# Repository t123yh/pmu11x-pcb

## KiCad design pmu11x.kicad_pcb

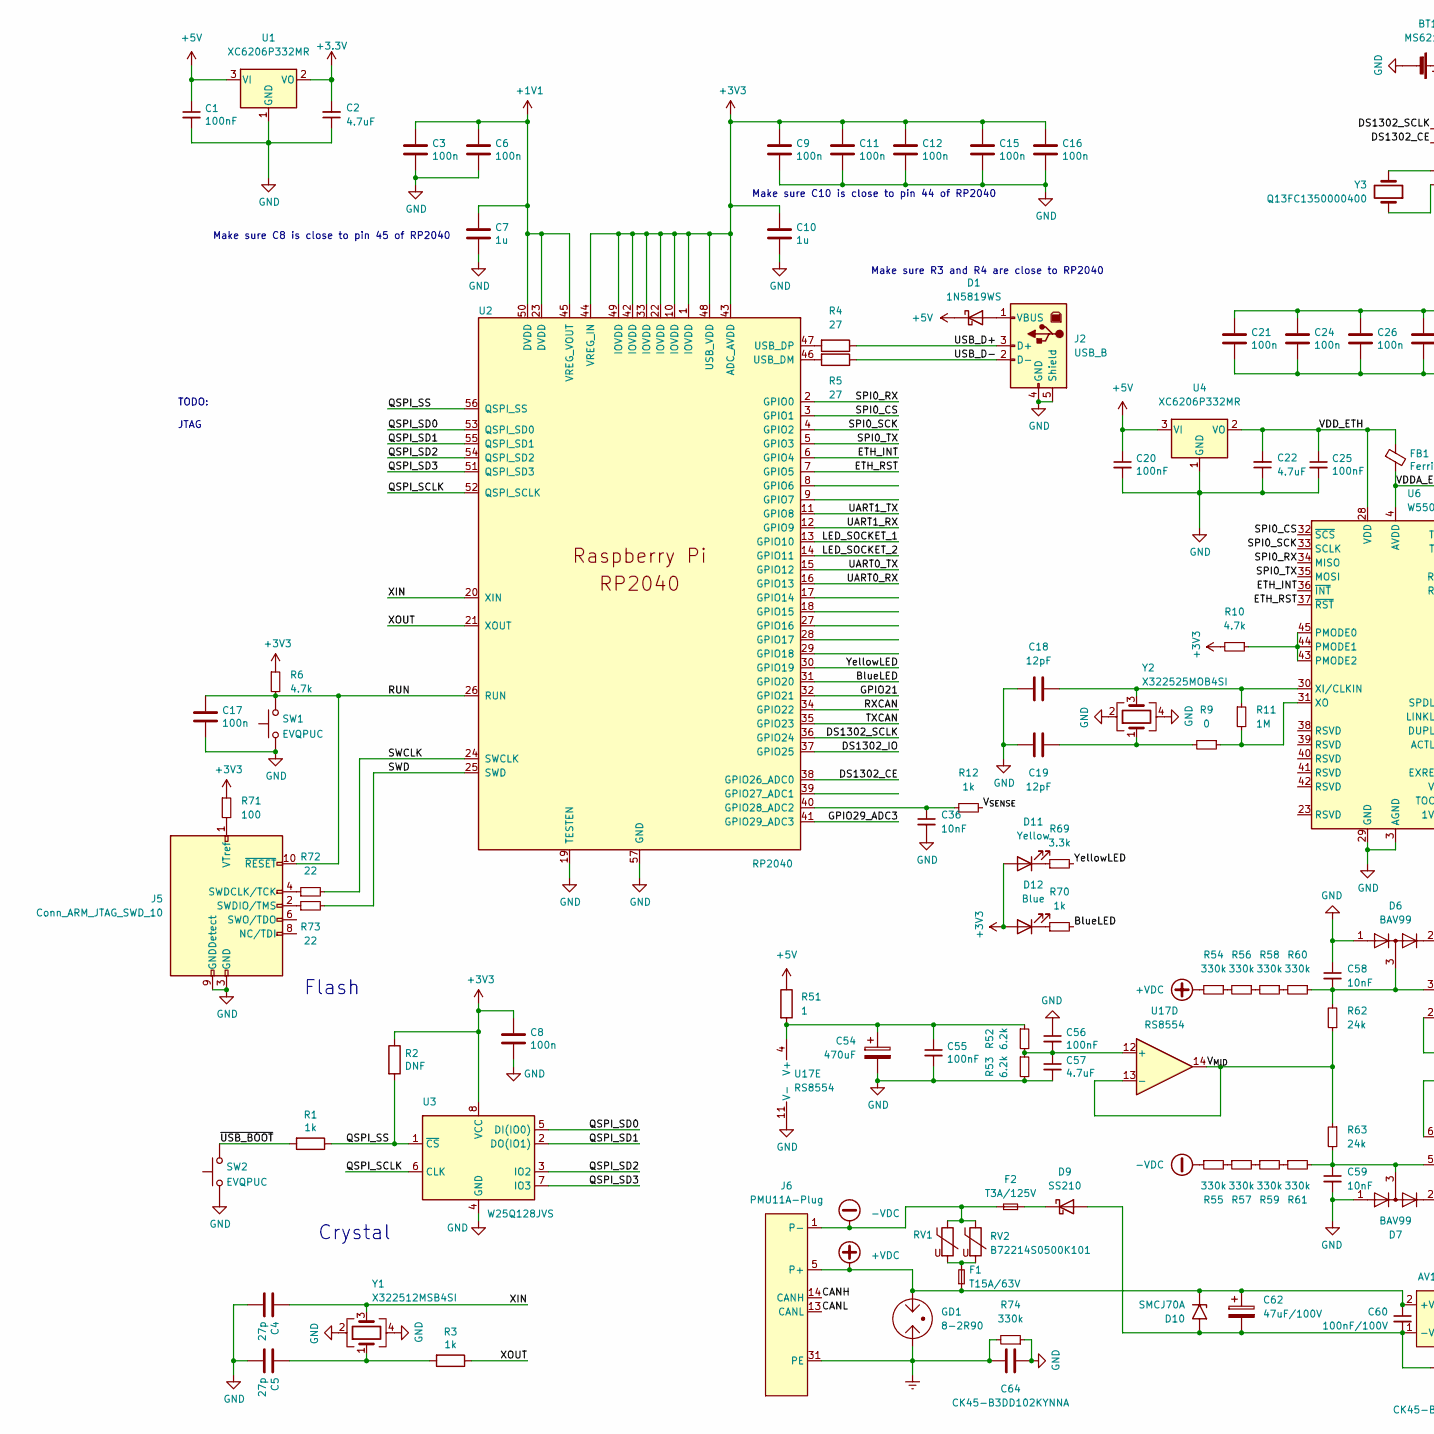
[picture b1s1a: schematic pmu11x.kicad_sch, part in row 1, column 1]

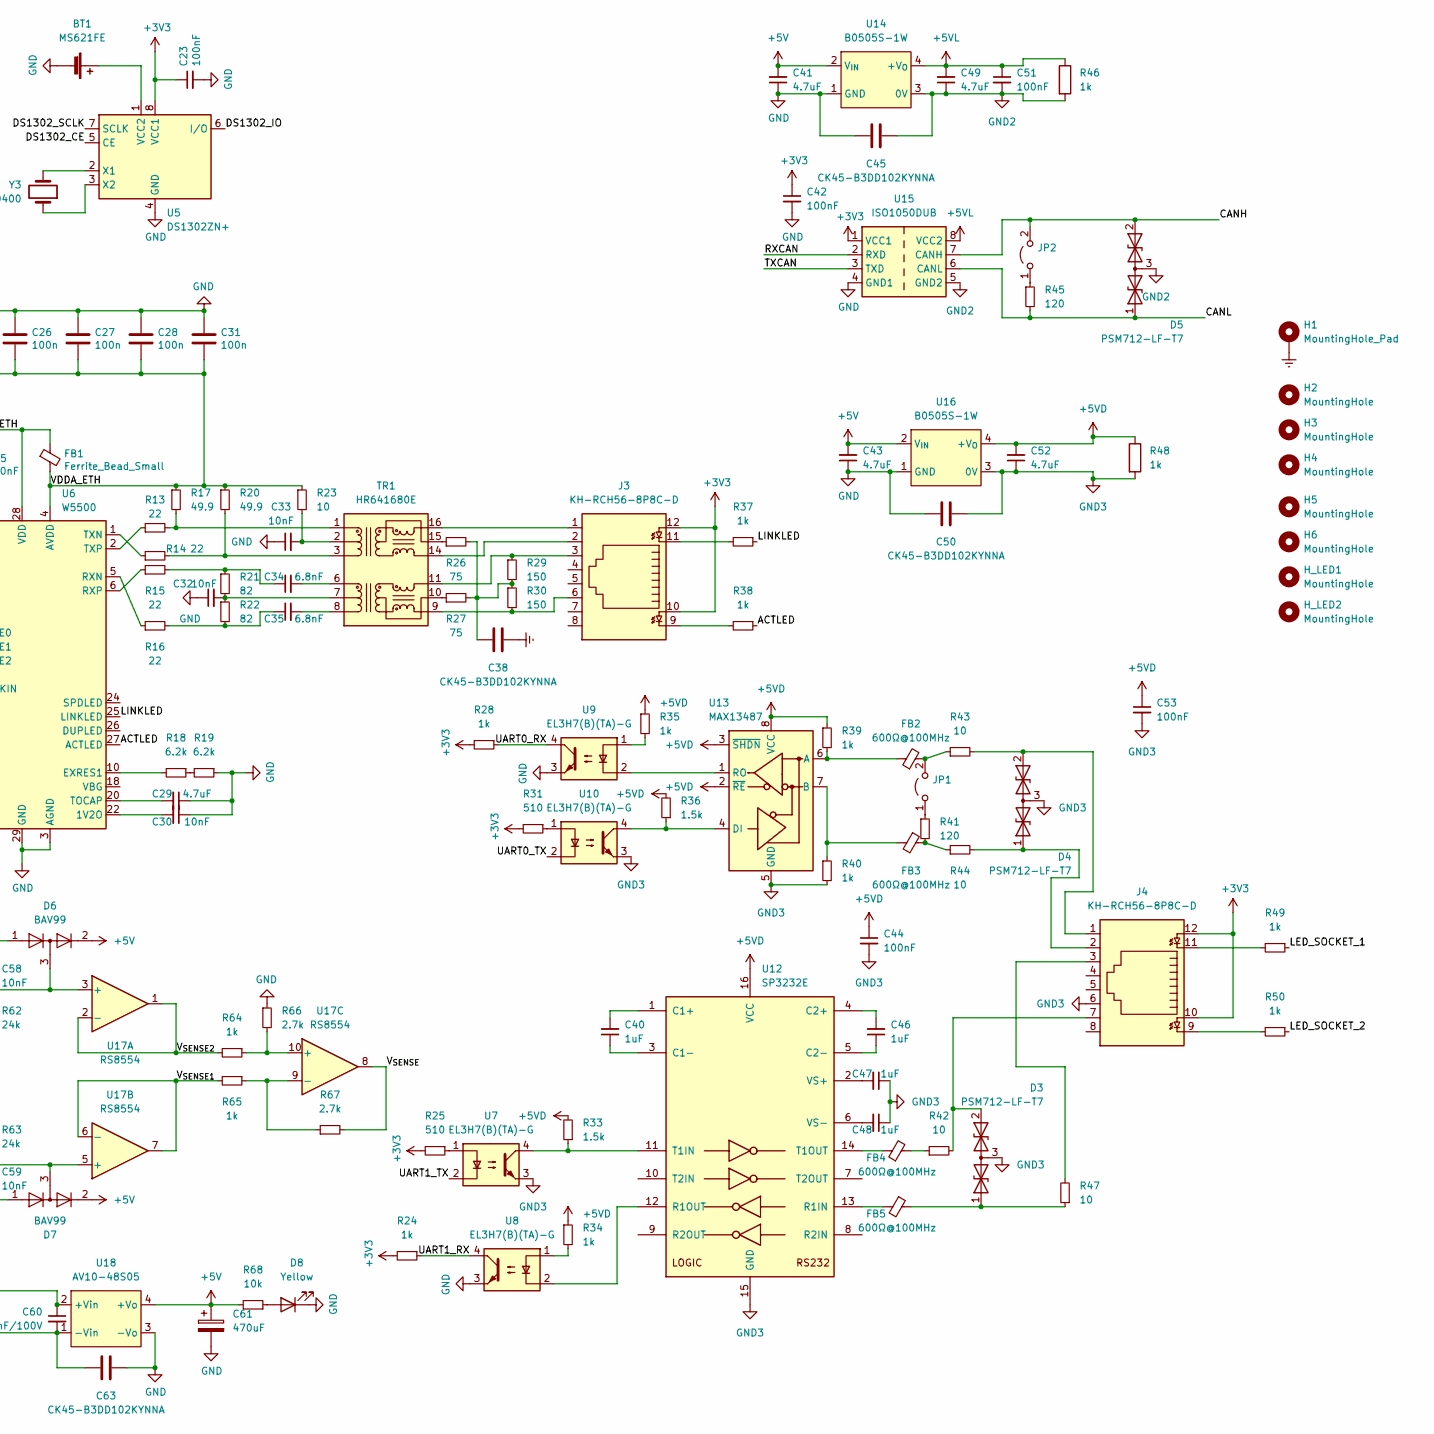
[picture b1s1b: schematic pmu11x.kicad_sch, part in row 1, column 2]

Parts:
BT1: MS621FE; BatteryHolder_Seiko_MS621F
C1: 100nF; 0603_C
C2, C22, C29, C41, C43, C49, C52, C57: 4.7uF; 0603_C
C3, C6, C8, C9, C11, C12, C15, C16, C17, C21, C24, C26, C27, C28, C31: 100n; 0402_C
C4, C5: 27p; 0402_C
C7, C10: 1u; 0402_C
C18, C19: 12pF; 0402_C
C20, C23, C25, C42, C44, C51, C53, C55, C56: 100nF; 0402_C
C30, C32, C33, C36: 10nF; 0402_C
C34, C35: 6.8nF; 0603_C
C38, C45, C50, C63, C64: CK45-B3DD102KYNNA; C_Disc_D7.5mm_W2.5mm_P5.00mm
C40, C46, C47, C48: 1uF; 0603_C
C54, C61: 470uF; CP_Radial_D6.3mm_P2.50mm
C58, C59: 10nF; 0603_C
C60: 100nF/100V; 0805_C
C62: 47uF/100V; CP_Radial_D8.0mm_P3.50mm
D1: 1N5819WS; SOD-323
D3, D4, D5: PSM712-LF-T7; SOT-23-3L
D6, D7: BAV99; SOT-23
D8, D11: Yellow; 0603_LED_S1_NUM
D9: SS210; D_SMA
D10: SMCJ70A; D_SMC
D12: Blue; 0603_LED_S1_NUM
F1: T15A/63V; Fuse_1812_4532Metric
F2: T3A/125V; Fuse_1812_4532Metric
FB1: Ferrite_Bead_Small; 0603_C
FB2, FB3, FB4, FB5: 600Ω@100MHz; 0603_R
GD1: 8-2R90; GDT_10KA
H1: MountingHole_Pad; MountingHole_3.5mm_Pad_Via
H2, H3, H4, H5, H6: MountingHole; MountingHole_3.5mm_Pad
H_LED1: MountingHole; MountingHole_3mm
H_LED2: MountingHole; MountingHole_2.2mm_M2
J2: USB_B; USB_B_OST_USB-B1HSxx_Horizontal
J3, J4: KH-RCH56-8P8C-D
J5: Conn_ARM_JTAG_SWD_10; PinSocket_2x05_P1.27mm_Vertical
J6: PMU11A-Plug
JP1, JP2: Jumper_2_Open; SolderJumper-2_P1.3mm_Open_RoundedPad1.0x1.5mm
R1, R3, R12, R24, R28, R34, R35, R37, R38, R39, R40, R49, R50, R64, R65, R70: 1k; 0402_R
R2: DNF; 0402_R
R4, R5: 27; 0402_R
R6, R10: 4.7k; 0402_R
R9: 0; 0402_R
R11: 1M; 0402_R
R13, R14, R15, R16, R72, R73: 22; 0402_R
R17, R20: 49.9; 0603_R
R18, R19, R52, R53: 6.2k; 0603_R
R21, R22: 82; 0603_R
R23: 10; 0402_R
R25, R31: 510; 0402_R
R26, R27: 75; 0603_R
R29, R30: 150; 0603_R
R33, R36: 1.5k; 0402_R
R41, R45: 120; 0603_R
R42, R43, R44, R47: 10; 0603_R
R46, R48: 1k; 0603_R
R51: 1; 0603_R
R54, R55, R56, R57, R58, R59, R60, R61, R74: 330k; 0805_R
R62, R63: 24k; 0805_R
R66, R67: 2.7k; 0603_R
R68: 10k; 0402_R
R69: 3.3k; 0402_R
R71: 100; 0402_R
RV1, RV2: B72214S0500K101; RV_Disc_D15.5mm_W4.6mm_P7.5mm
SW1, SW2: EVQPUC; Panasonic_EVQPUL_EVQPUC
TR1: HR641680E; Transformer_Ethernet_Bourns_PT61017PEL
U1, U4: XC6206P332MR; SOT-23-3L
U2: RP2040; RP2040-QFN-56
U3: W25Q128JVS; SOIC-8_5.23x5.23mm_P1.27mm
U5: DS1302ZN+; SOIC-8_3.9x4.9mm_P1.27mm
U6: W5500; LQFP-48_7x7mm_P0.5mm
U7, U8, U9, U10: EL3H7(B)(TA)-G; SOP-4_4.4x2.6mm_P1.27mm
U12: SP3232E; SOIC-16_3.9x9.9mm_P1.27mm
U13: MAX13487; SOIC-8_3.9x4.9mm_P1.27mm
U14, U16: B0505S-1W; B_S-1W
U15: ISO1050DUB; SOP-8_6.62x9.15mm_P2.54mm
U17: RS8554; TSSOP-14_4.4x5mm_P0.65mm
U18: AV10-48S05; AV10-48Sxx
Y1: X322512MSB4SI; Oscillator_SMD_Abracon_ASE-4Pin_3.2x2.5mm
Y2: X322525MOB4SI; Oscillator_SMD_Abracon_ASE-4Pin_3.2x2.5mm
Y3: Q13FC1350000400; Crystal_SMD_3215-2Pin_3.2x1.5mm

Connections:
+1V1: C3.1, C6.1, C7.1, U2.23 (DVDD), U2.45 (VREG_VOUT), U2.50 (DVDD)
+5V: C1.1, C20.1, C41.2, C43.2, C61.1, D1.1 (K), D6.2 (A), D7.2 (A), R51.1, R68.2, U1.3 (VI), U4.3 (VI), U14.2 (V_{IN}), U16.2 (V_{IN}), U18.4 (+Vo)
+5VD: C44.1, C52.2, C53.1, R33.2, R34.1, R35.1, R36.2, R39.1, R48.1, U12.16 (VCC), U13.2 (~RE), U13.3 (~SHDN), U13.8 (VCC), U16.4 (+V_{O})
+5VL: C49.2, C51.1, R46.1, U14.4 (+V_{O}), U15.8 (VCC2)
+VDC: C60.1, C62.1, D10.1 (A1), F1.1, GD1.3, J6.5 (P+), R54.2, U18.2 (+Vin)
-VDC: F2.2, J6.1 (P-), R55.1, RV1.1, RV2.1
/ACTLED: R38.1, U6.27 (ACTLED)
/BlueLED: R70.2, U2.31 (GPIO20)
/CANH: D5.2 (A2), J6.14 (CANH), JP2.2 (B), U15.7 (CANH)
/CANL: D5.1 (A1), J6.13 (CANL), R45.2, U15.6 (CANL)
/DS1302_CE: U2.38 (GPIO26_ADC0), U5.5 (CE)
/DS1302_IO: U2.37 (GPIO25), U5.6 (I/O)
/DS1302_SCLK: U2.36 (GPIO24), U5.7 (SCLK)
/ETH_INT: U2.6 (GPIO4), U6.36 (~INT)
/ETH_RST: U2.7 (GPIO5), U6.37 (~RST)
/GPIO21: U2.32 (GPIO21)
/GPIO29_ADC3: U2.41 (GPIO29_ADC3)
/LED_SOCKET_1: R49.1, U2.13 (GPIO10)
/LED_SOCKET_2: R50.1, U2.14 (GPIO11)
/LINKLED: R37.1, U6.25 (LINKLED)
/QSPI_SCLK: U2.52 (QSPI_SCLK), U3.6 (CLK)
/QSPI_SD0: U2.53 (QSPI_SD0), U3.5 (DI(IO0))
/QSPI_SD1: U2.55 (QSPI_SD1), U3.2 (DO(IO1))
/QSPI_SD2: U2.54 (QSPI_SD2), U3.3 (IO2)
/QSPI_SD3: U2.51 (QSPI_SD3), U3.7 (IO3)
/QSPI_SS: R1.1, R2.2, U2.56 (QSPI_SS), U3.1 (~CS)
/RUN: C17.1, J5.10 (~RESET), R6.2, SW1.2, U2.26 (RUN)
/RXCAN: U2.34 (GPIO22), U15.2 (RXD)
/SPI0_CS: U2.3 (GPIO1), U6.32 (~SCS)
/SPI0_RX: U2.2 (GPIO0), U6.34 (MISO)
/SPI0_SCK: U2.4 (GPIO2), U6.33 (SCLK)
/SPI0_TX: U2.5 (GPIO3), U6.35 (MOSI)
/SWCLK: R72.2, U2.24 (SWCLK)
/SWD: R73.2, U2.25 (SWD)
/TXCAN: U2.35 (GPIO23), U15.3 (TXD)
/UART0_RX: R28.1, U2.16 (GPIO13), U9.4
/UART0_TX: U2.15 (GPIO12), U10.2
/UART1_RX: R24.1, U2.12 (GPIO9), U8.4
/UART1_TX: U2.11 (GPIO8), U7.2
/USB_D+: J2.3 (D+), R4.1
/USB_D-: J2.2 (D-), R5.1
/VDDA_ETH: C21.2, C24.2, C26.2, C27.2, C28.2, C31.2, FB1.2, R17.1, R20.1, R23.1, U6.4 (AVDD), U6.8 (AVDD), U6.11 (AVDD), U6.15 (AVDD), U6.17 (AVDD), U6.21 (AVDD)
/VDD_ETH: C22.2, C25.1, FB1.1, U4.2 (VO), U6.28 (VDD)
/V_{MID}: R62.1, R63.1, U17.13 (-), U17.14
/V_{SENSE1}: R65.2, U17.6 (-), U17.7
/V_{SENSE2}: R64.2, U17.1, U17.2 (-)
/V_{SENSE}: R12.2, R67.2, U17.8
/XIN: C4.1, U2.20 (XIN), Y1.3
/XOUT: R3.1, U2.21 (XOUT)
/YellowLED: R69.2, U2.30 (GPIO19)
/~USB_BOOT: R1.2, SW2.2
Earth: C38.2, C64.1, GD1.1, H1.1, J6.29 (PE), J6.31 (PE), J6.32 (PE), R74.2
GND: BT1.2 (-), C1.2, C2.1, C3.2, C4.2, C5.2, C6.2, C7.2, C8.2, C9.2, C10.2, C11.2, C12.2, C15.2, C16.2, C17.2, C18.2, C19.2, C20.2, C21.1, C22.1, C23.2, C24.1, C25.2, C26.1, C27.1, C28.1, C29.1, C30.1, C31.1, C32.1, C33.1, C36.2, C41.1, C42.2, C43.1, C45.1, C50.1, C54.2, C55.2, C56.1, C57.2, C58.1, C59.2, C61.2, C63.2, C64.2, D6.1 (K), D7.1 (K), D8.1 (K), J2.4 (GND), J2.5 (Shield), J5.3 (GND), J5.5 (GND), J5.9 (GNDDetect), R19.1, R53.2, R66.1, R74.1, SW1.1, SW2.1, U1.1 (GND), U2.19 (TESTEN), U2.57 (GND), U3.4 (GND), U4.1 (GND), U5.4 (GND), U6.3 (AGND), U6.9 (AGND), U6.14 (AGND), U6.16 (AGND), U6.19 (AGND), U6.29 (GND), U6.48 (AGND), U8.3, U9.3, U14.1 (GND), U15.4 (GND1), U16.1 (GND), U17.11 (V-), U18.3 (-Vo), Y1.2, Y1.4, Y2.2, Y2.4
GND2: C45.2, C49.1, C51.2, D5.3 (common), R46.2, U14.3 (0V), U15.5 (GND2)
GND3: C44.2, C47.1, C48.1, C50.2, C52.1, C53.2, D3.3 (common), D4.3 (common), J4.6, R40.2, R48.2, U7.3, U10.3, U12.15 (GND), U13.5 (GND), U13.9 (GND), U16.3 (0V)
unnamed: BT1.1 (+), U5.1 (VCC2)
unnamed: C5.1, R3.2, Y1.1
unnamed: C18.1, R11.1, U6.30 (XI/CLKIN), Y2.3
unnamed: C19.1, R9.2, Y2.1
unnamed: C29.2, U6.20 (TOCAP)
unnamed: C30.2, U6.22 (1V2O)
unnamed: C32.2, R21.2, R22.1, TR1.7 (C_RD)
unnamed: C33.2, R23.2, TR1.2 (C_TD)
unnamed: C34.1, R15.2, R21.1
unnamed: C34.2, TR1.6 (RD+)
unnamed: C35.1, R16.2, R22.2
unnamed: C35.2, TR1.8 (RD-)
unnamed: C36.1, R12.1, U2.40 (GPIO28_ADC2)
unnamed: C38.1, R26.2, R27.2, R29.2, R30.1
unnamed: C40.1, U12.3 (C1-)
unnamed: C40.2, U12.1 (C1+)
unnamed: C46.1, U12.5 (C2-)
unnamed: C46.2, U12.4 (C2+)
unnamed: C47.2, U12.2 (VS+)
unnamed: C48.2, U12.6 (VS-)
unnamed: C54.1, C55.1, R51.2, R52.1, U17.4 (V+)
unnamed: C56.2, C57.1, R52.2, R53.1, U17.12 (+)
unnamed: C58.2, D6.3 (K), R60.1, R62.2, U17.3 (+)
unnamed: C59.1, D7.3 (K), R61.2, R63.2, U17.5 (+)
unnamed: C60.2, C62.2, C63.1, D9.2 (A), D10.2 (A2), U18.1 (-Vin)
unnamed: D1.2 (A), J2.1 (VBUS)
unnamed: D3.1 (A1), FB5.1, R47.1
unnamed: D3.2 (A2), J4.7, R42.2
unnamed: D4.1 (A1), J4.2, R44.2
unnamed: D4.2 (A2), J4.1, R43.2
unnamed: D8.2 (A), R68.1
unnamed: D9.1 (K), F2.1
unnamed: D11.1 (K), R69.1
unnamed: D12.1 (K), R70.1
unnamed: F1.2, RV1.2, RV2.2
unnamed: FB2.1, R39.2, U13.6 (A)
unnamed: FB2.2, JP1.2 (B), R43.1
unnamed: FB3.1, R41.2, R44.1
unnamed: FB3.2, R40.1, U13.7 (B)
unnamed: FB4.1, U12.14 (T1OUT)
unnamed: FB4.2, R42.1
unnamed: FB5.2, U12.13 (R1IN)
unnamed: J3.1, TR1.16 (TX+)
unnamed: J3.2, TR1.14 (TX-)
unnamed: J3.3, R29.1, TR1.11 (RX+)
unnamed: J3.6, R30.2, TR1.9 (RX-)
unnamed: J3.9, R38.2
unnamed: J3.11, R37.2
unnamed: J4.3, R47.2
unnamed: J4.9, R50.2
unnamed: J4.11, R49.2
unnamed: J5.1 (VTref), R71.2
unnamed: J5.2 (SWDIO/TMS), R73.1
unnamed: J5.4 (SWDCLK/TCK), R72.1
unnamed: JP1.1 (A), R41.1
unnamed: JP2.1 (A), R45.1
unnamed: R4.2, U2.47 (USB_DP)
unnamed: R5.2, U2.46 (USB_DM)
unnamed: R10.1, U6.43 (PMODE2), U6.44 (PMODE1), U6.45 (PMODE0)
unnamed: R9.1, R11.2, U6.31 (XO)
unnamed: R13.1, U6.2 (TXP)
unnamed: R13.2, R17.2, TR1.1 (TD+)
unnamed: R14.1, U6.1 (TXN)
unnamed: R14.2, R20.2, TR1.3 (TD-)
unnamed: R15.1, U6.6 (RXP)
unnamed: R16.1, U6.5 (RXN)
unnamed: R18.1, R19.2
unnamed: R18.2, U6.10 (EXRES1)
unnamed: R25.1, U7.1
unnamed: R26.1, TR1.15 (C_TX)
unnamed: R27.1, TR1.10 (C_RX)
unnamed: R31.1, U10.1
unnamed: R33.1, U7.4, U12.11 (T1IN)
unnamed: R34.2, U8.1
unnamed: R35.2, U9.1
unnamed: R36.1, U10.4, U13.4 (DI)
unnamed: R54.1, R56.2
unnamed: R55.2, R57.1
unnamed: R56.1, R58.2
unnamed: R57.2, R59.1
unnamed: R58.1, R60.2
unnamed: R59.2, R61.1
unnamed: R64.1, R66.2, U17.10 (+)
unnamed: R65.1, R67.1, U17.9 (-)
unnamed: U5.2 (X1), Y3.2
unnamed: U5.3 (X2), Y3.1
unnamed: U8.2, U12.12 (R1OUT)
unnamed: U9.2, U13.1 (RO)

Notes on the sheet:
Make sure C8 is close to pin 45 of RP2040
Crystal
Make sure C10 is close to pin 44 of RP2040
Make sure R3 and R4 are close to RP2040
Flash
TODO: JTAG

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
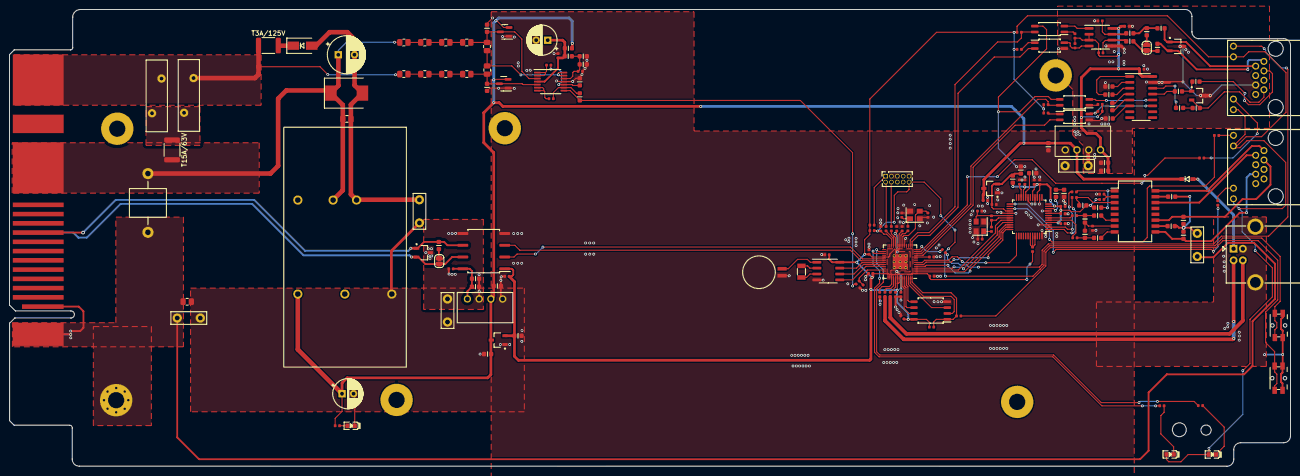
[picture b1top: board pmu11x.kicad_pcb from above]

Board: 2 copper layers, 276.9 x 98.7 mm, 191 parts (0 on the bottom side), 142 nets.

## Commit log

2023-01-26 Initial
